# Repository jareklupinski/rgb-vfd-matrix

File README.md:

# rgb-vfd-matrix
An interface board for displaying images on a unique display

Trawling ebay one day I stumbled across the IGG4-64x64M2. It seemed like an interesting piece and a good challenge, so I designed a board to easily feed it pixel data from any microcontroller.

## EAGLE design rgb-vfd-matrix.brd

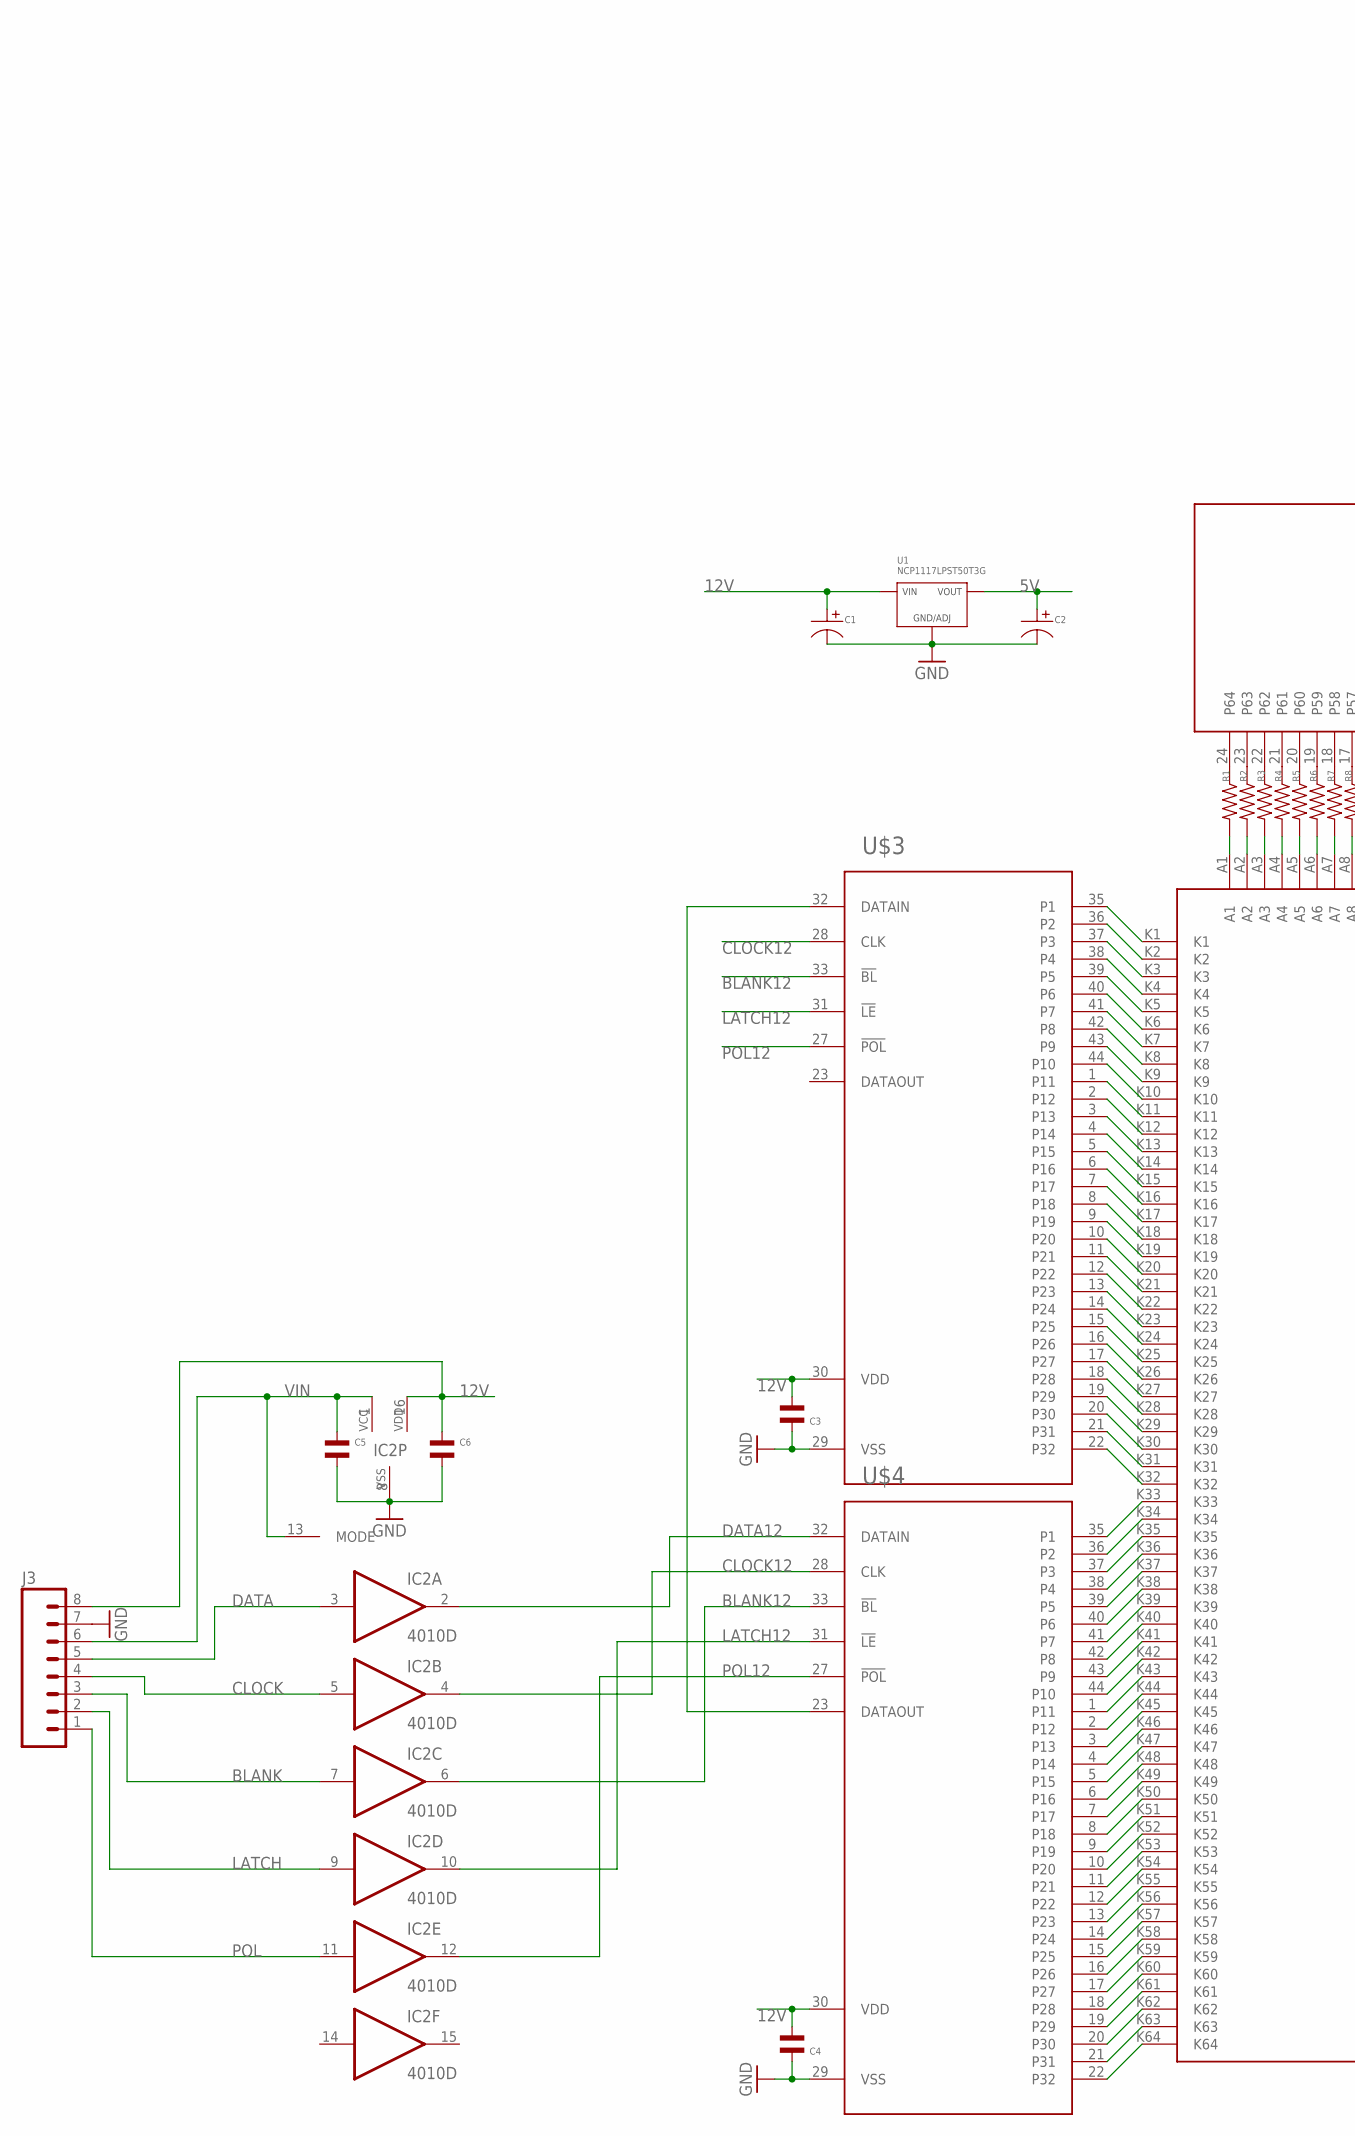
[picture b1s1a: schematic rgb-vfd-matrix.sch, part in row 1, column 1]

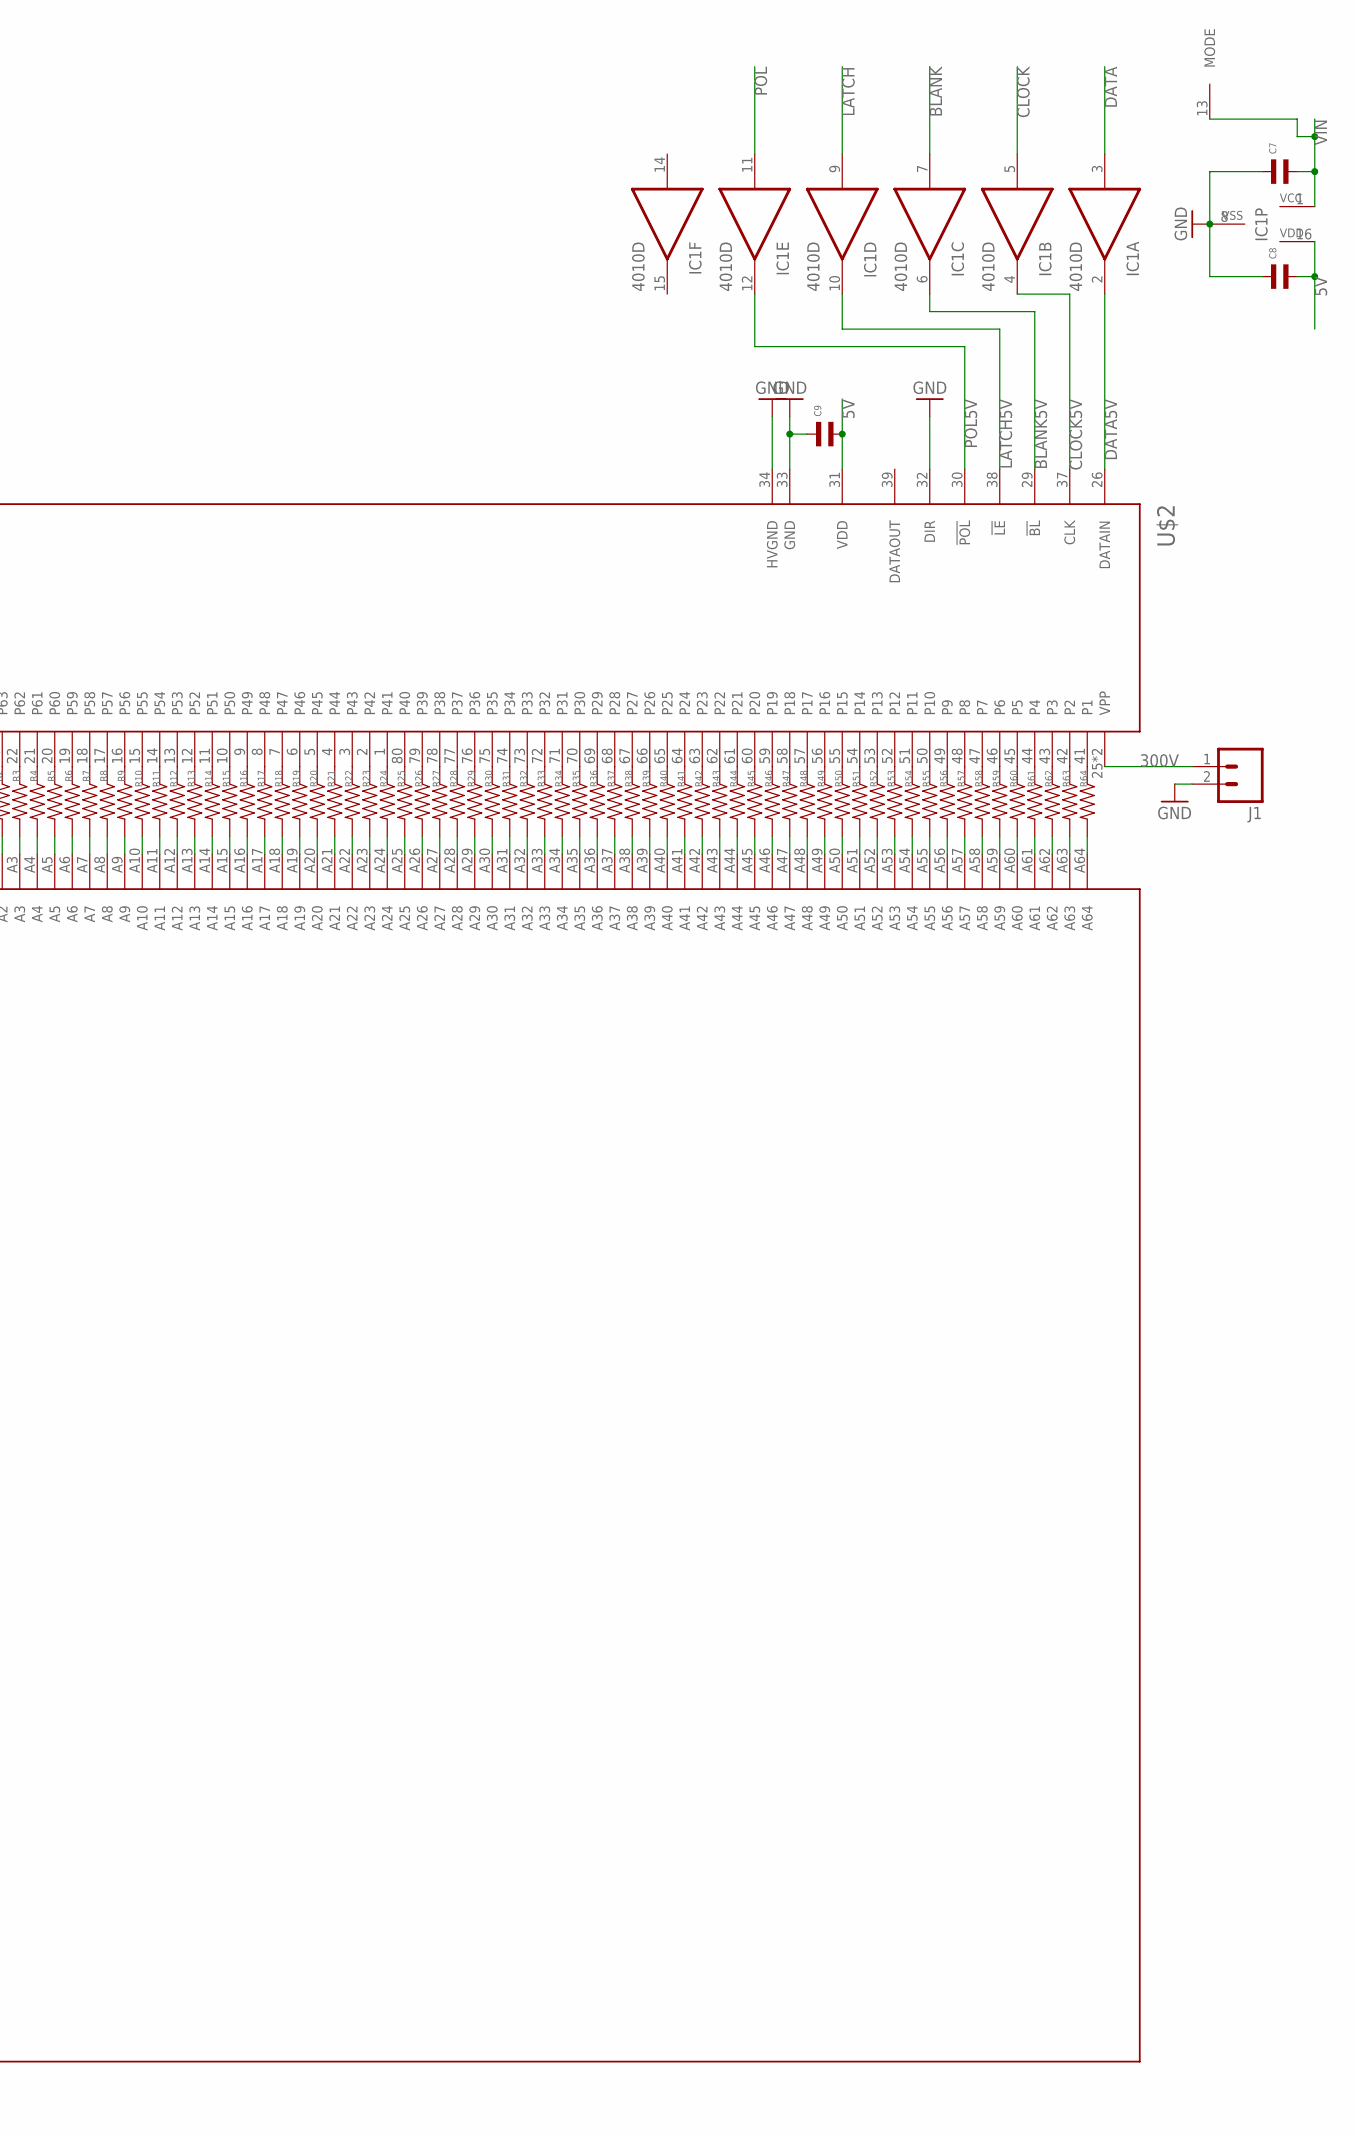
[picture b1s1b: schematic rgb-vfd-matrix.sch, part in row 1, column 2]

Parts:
C1, C2: CAPACITOR_P_8MM; CP8MM
C3, C4, C5, C6, C7, C8, C9: CAPACITOR_NP_0603; C0603
IC1, IC2: 4010D; SO16
J1: M023.5MM; SCREWTERMINAL-3.5MM-2
J3: M083.5MM-8; SCREWTERMINAL-3.5MM-8
R1, R2, R3, R4, R5, R6, R7, R8, R9, R10, R11, R12, R13, R14, R15, R16, R17, R18, R19, R20, R21, R22, R23, R24, R25, R26, R27, R28, R29, R30, R31, R32, R33, R34, R35, R36, R37, R38, R39, R40, R41, R42, R43, R44, R45, R46, R47, R48, R49, R50, R51, R52, R53, R54, R55, R56, R57, R58, R59, R60, R61, R62, R63, R64: RESISTOR_0805; R0805
U1: NCP1117LPST50T3G; SOT-223-3
U$1: RGBVFDMATRIX
U$2: HV507; PQFP80
U$3, U$4: HV5530; PQFP44

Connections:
5V: C2.P$1, C8.P$2, C9.P$2, IC1.16 (VDD), U1.P$1 (VOUT), U1.P$3 (VOUT), U$2.31 (VDD)
12V: C1.P$1, C3.P$2, C4.P$2, C6.P$1, IC2.16 (VDD), J3.8, U1.P$4 (VIN), U$3.30 (VDD), U$4.30 (VDD)
300V: J1.1, U$2.25 (VPP), U$2.40 (VPP)
BLANK: IC1.7 (I), IC2.7 (I), J3.3
BLANK5V: IC1.6 (O), U$2.29 (!BL)
BLANK12: IC2.6 (O), U$3.33 (!BL), U$4.33 (!BL)
CLOCK: IC1.5 (I), IC2.5 (I), J3.4
CLOCK5V: IC1.4 (O), U$2.37 (CLK)
CLOCK12: IC2.4 (O), U$3.28 (CLK), U$4.28 (CLK)
DATA: IC1.3 (I), IC2.3 (I), J3.5
DATA5V: IC1.2 (O), U$2.26 (DATAIN)
DATA12: IC2.2 (O), U$4.32 (DATAIN)
GND: C1.P$2, C2.P$2, C3.P$1, C4.P$1, C5.P$2, C6.P$2, C7.P$1, C8.P$1, C9.P$1, IC1.8 (VSS), IC2.8 (VSS), J1.2, J3.7, U1.P$2 (GND/ADJ), U$2.32 (DIR), U$2.33 (GND), U$2.34 (HVGND), U$3.29 (VSS), U$4.29 (VSS)
LATCH: IC1.9 (I), IC2.9 (I), J3.2
LATCH5V: IC1.10 (O), U$2.38 (!LE)
LATCH12: IC2.10 (O), U$3.31 (!LE), U$4.31 (!LE)
unnamed: R1.P$2, U$1.A1
unnamed: R2.P$2, U$1.A2
unnamed: R3.P$2, U$1.A3
unnamed: R4.P$2, U$1.A4
unnamed: R5.P$2, U$1.A5
unnamed: R6.P$2, U$1.A6
unnamed: R7.P$2, U$1.A7
unnamed: R8.P$2, U$1.A8
unnamed: R9.P$2, U$1.A9
unnamed: R10.P$2, U$1.A10
unnamed: R11.P$2, U$1.A11
unnamed: R12.P$2, U$1.A12
unnamed: R13.P$2, U$1.A13
unnamed: R14.P$2, U$1.A14
unnamed: R15.P$2, U$1.A15
unnamed: R16.P$2, U$1.A16
unnamed: R17.P$2, U$1.A17
unnamed: R18.P$2, U$1.A18
unnamed: R19.P$2, U$1.A19
unnamed: R20.P$2, U$1.A20
unnamed: R21.P$2, U$1.A21
unnamed: R22.P$2, U$1.A22
unnamed: R23.P$2, U$1.A23
unnamed: R24.P$2, U$1.A24
unnamed: R25.P$2, U$1.A25
unnamed: R26.P$2, U$1.A26
unnamed: R27.P$2, U$1.A27
unnamed: R28.P$2, U$1.A28
unnamed: R29.P$2, U$1.A29
unnamed: R30.P$2, U$1.A30
unnamed: R31.P$2, U$1.A31
unnamed: R32.P$2, U$1.A32
unnamed: R33.P$2, U$1.A33
unnamed: R34.P$2, U$1.A34
unnamed: R35.P$2, U$1.A35
unnamed: R36.P$2, U$1.A36
unnamed: R37.P$2, U$1.A37
unnamed: R38.P$2, U$1.A38
unnamed: R39.P$2, U$1.A39
unnamed: R40.P$2, U$1.A40
unnamed: R41.P$2, U$1.A41
unnamed: R42.P$2, U$1.A42
unnamed: R43.P$2, U$1.A43
unnamed: R44.P$2, U$1.A44
unnamed: R45.P$2, U$1.A45
unnamed: R46.P$2, U$1.A46
unnamed: R47.P$2, U$1.A47
unnamed: R48.P$2, U$1.A48
unnamed: R49.P$2, U$1.A49
unnamed: R50.P$2, U$1.A50
unnamed: R51.P$2, U$1.A51
unnamed: R52.P$2, U$1.A52
unnamed: R53.P$2, U$1.A53
unnamed: R54.P$2, U$1.A54
unnamed: R55.P$2, U$1.A55
unnamed: R56.P$2, U$1.A56
unnamed: R57.P$2, U$1.A57
unnamed: R58.P$2, U$1.A58
unnamed: R59.P$2, U$1.A59
unnamed: R60.P$2, U$1.A60
unnamed: R61.P$2, U$1.A61
unnamed: R62.P$2, U$1.A62
unnamed: R63.P$2, U$1.A63
unnamed: R64.P$2, U$1.A64
unnamed: R1.P$1, U$2.24 (P64)
unnamed: U$1.K1, U$3.35 (P1)
unnamed: R2.P$1, U$2.23 (P63)
unnamed: R3.P$1, U$2.22 (P62)
unnamed: R4.P$1, U$2.21 (P61)
unnamed: R5.P$1, U$2.20 (P60)
unnamed: R6.P$1, U$2.19 (P59)
unnamed: R7.P$1, U$2.18 (P58)
unnamed: R8.P$1, U$2.17 (P57)
unnamed: R9.P$1, U$2.16 (P56)
unnamed: R10.P$1, U$2.15 (P55)
unnamed: R11.P$1, U$2.14 (P54)
unnamed: R12.P$1, U$2.13 (P53)
unnamed: R13.P$1, U$2.12 (P52)
unnamed: R14.P$1, U$2.11 (P51)
unnamed: R15.P$1, U$2.10 (P50)
unnamed: R16.P$1, U$2.9 (P49)
unnamed: R17.P$1, U$2.8 (P48)
unnamed: R18.P$1, U$2.7 (P47)
unnamed: R19.P$1, U$2.6 (P46)
unnamed: R20.P$1, U$2.5 (P45)
unnamed: R21.P$1, U$2.4 (P44)
unnamed: R22.P$1, U$2.3 (P43)
unnamed: R23.P$1, U$2.2 (P42)
unnamed: R24.P$1, U$2.1 (P41)
unnamed: R25.P$1, U$2.80 (P40)
unnamed: R26.P$1, U$2.79 (P39)
unnamed: R27.P$1, U$2.78 (P38)
unnamed: R28.P$1, U$2.77 (P37)
unnamed: R29.P$1, U$2.76 (P36)
unnamed: R30.P$1, U$2.75 (P35)
unnamed: R31.P$1, U$2.74 (P34)
unnamed: R32.P$1, U$2.73 (P33)
unnamed: R33.P$1, U$2.72 (P32)
unnamed: R34.P$1, U$2.71 (P31)
unnamed: R35.P$1, U$2.70 (P30)
unnamed: R36.P$1, U$2.69 (P29)
unnamed: R37.P$1, U$2.68 (P28)
unnamed: R38.P$1, U$2.67 (P27)
unnamed: R39.P$1, U$2.66 (P26)
unnamed: R40.P$1, U$2.65 (P25)
unnamed: R41.P$1, U$2.64 (P24)
unnamed: R42.P$1, U$2.63 (P23)
unnamed: R43.P$1, U$2.62 (P22)
unnamed: R44.P$1, U$2.61 (P21)
unnamed: R45.P$1, U$2.60 (P20)
unnamed: R46.P$1, U$2.59 (P19)
unnamed: R47.P$1, U$2.58 (P18)
unnamed: R48.P$1, U$2.57 (P17)
unnamed: R49.P$1, U$2.56 (P16)
unnamed: R50.P$1, U$2.55 (P15)
unnamed: R51.P$1, U$2.54 (P14)
unnamed: R52.P$1, U$2.53 (P13)
unnamed: R53.P$1, U$2.52 (P12)
unnamed: R54.P$1, U$2.51 (P11)
unnamed: R55.P$1, U$2.50 (P10)
unnamed: R56.P$1, U$2.49 (P9)
unnamed: R57.P$1, U$2.48 (P8)
unnamed: R58.P$1, U$2.47 (P7)
unnamed: R59.P$1, U$2.46 (P6)
unnamed: R60.P$1, U$2.45 (P5)
unnamed: R61.P$1, U$2.44 (P4)
unnamed: R62.P$1, U$2.43 (P3)
unnamed: R63.P$1, U$2.42 (P2)
unnamed: R64.P$1, U$2.41 (P1)
unnamed: U$1.K2, U$3.36 (P2)
unnamed: U$1.K3, U$3.37 (P3)
unnamed: U$1.K4, U$3.38 (P4)
unnamed: U$1.K5, U$3.39 (P5)
unnamed: U$1.K6, U$3.40 (P6)
unnamed: U$1.K7, U$3.41 (P7)
unnamed: U$1.K8, U$3.42 (P8)
unnamed: U$1.K9, U$3.43 (P9)
unnamed: U$1.K10, U$3.44 (P10)
unnamed: U$1.K11, U$3.1 (P11)
unnamed: U$1.K12, U$3.2 (P12)
unnamed: U$1.K13, U$3.3 (P13)
unnamed: U$1.K14, U$3.4 (P14)
unnamed: U$1.K15, U$3.5 (P15)
unnamed: U$1.K16, U$3.6 (P16)
unnamed: U$1.K17, U$3.7 (P17)
unnamed: U$1.K18, U$3.8 (P18)
unnamed: U$1.K19, U$3.9 (P19)
unnamed: U$1.K20, U$3.10 (P20)
unnamed: U$1.K21, U$3.11 (P21)
unnamed: U$1.K22, U$3.12 (P22)
unnamed: U$1.K23, U$3.13 (P23)
unnamed: U$1.K24, U$3.14 (P24)
unnamed: U$1.K25, U$3.15 (P25)
unnamed: U$1.K26, U$3.16 (P26)
unnamed: U$1.K27, U$3.17 (P27)
unnamed: U$1.K28, U$3.18 (P28)
unnamed: U$1.K29, U$3.19 (P29)
unnamed: U$1.K30, U$3.20 (P30)
unnamed: U$1.K31, U$3.21 (P31)
unnamed: U$1.K32, U$3.22 (P32)
unnamed: U$1.K33, U$4.35 (P1)
unnamed: U$1.K34, U$4.36 (P2)
unnamed: U$1.K35, U$4.37 (P3)
unnamed: U$1.K36, U$4.38 (P4)
unnamed: U$1.K37, U$4.39 (P5)
unnamed: U$1.K38, U$4.40 (P6)
unnamed: U$1.K39, U$4.41 (P7)
unnamed: U$1.K40, U$4.42 (P8)
unnamed: U$1.K41, U$4.43 (P9)
unnamed: U$1.K42, U$4.44 (P10)
unnamed: U$1.K43, U$4.1 (P11)
unnamed: U$1.K44, U$4.2 (P12)
unnamed: U$1.K45, U$4.3 (P13)
unnamed: U$1.K46, U$4.4 (P14)
unnamed: U$1.K47, U$4.5 (P15)
unnamed: U$1.K48, U$4.6 (P16)
unnamed: U$1.K49, U$4.7 (P17)
unnamed: U$1.K50, U$4.8 (P18)
unnamed: U$1.K51, U$4.9 (P19)
unnamed: U$1.K52, U$4.10 (P20)
unnamed: U$1.K53, U$4.11 (P21)
unnamed: U$1.K54, U$4.12 (P22)
unnamed: U$1.K55, U$4.13 (P23)
unnamed: U$1.K56, U$4.14 (P24)
unnamed: U$1.K57, U$4.15 (P25)
unnamed: U$1.K58, U$4.16 (P26)
unnamed: U$1.K59, U$4.17 (P27)
unnamed: U$1.K60, U$4.18 (P28)
unnamed: U$1.K61, U$4.19 (P29)
unnamed: U$1.K62, U$4.20 (P30)
unnamed: U$1.K63, U$4.21 (P31)
unnamed: U$3.32 (DATAIN), U$4.23 (DATAOUT)
unnamed: U$1.K64, U$4.22 (P32)
POL: IC1.11 (I), IC2.11 (I), J3.1
POL5V: IC1.12 (O), U$2.30 (!POL)
POL12: IC2.12 (O), U$3.27 (!POL), U$4.27 (!POL)
VIN: C5.P$1, C7.P$2, IC1.1 (VCC), IC1.13 (MODE), IC2.1 (VCC), IC2.13 (MODE), J3.6

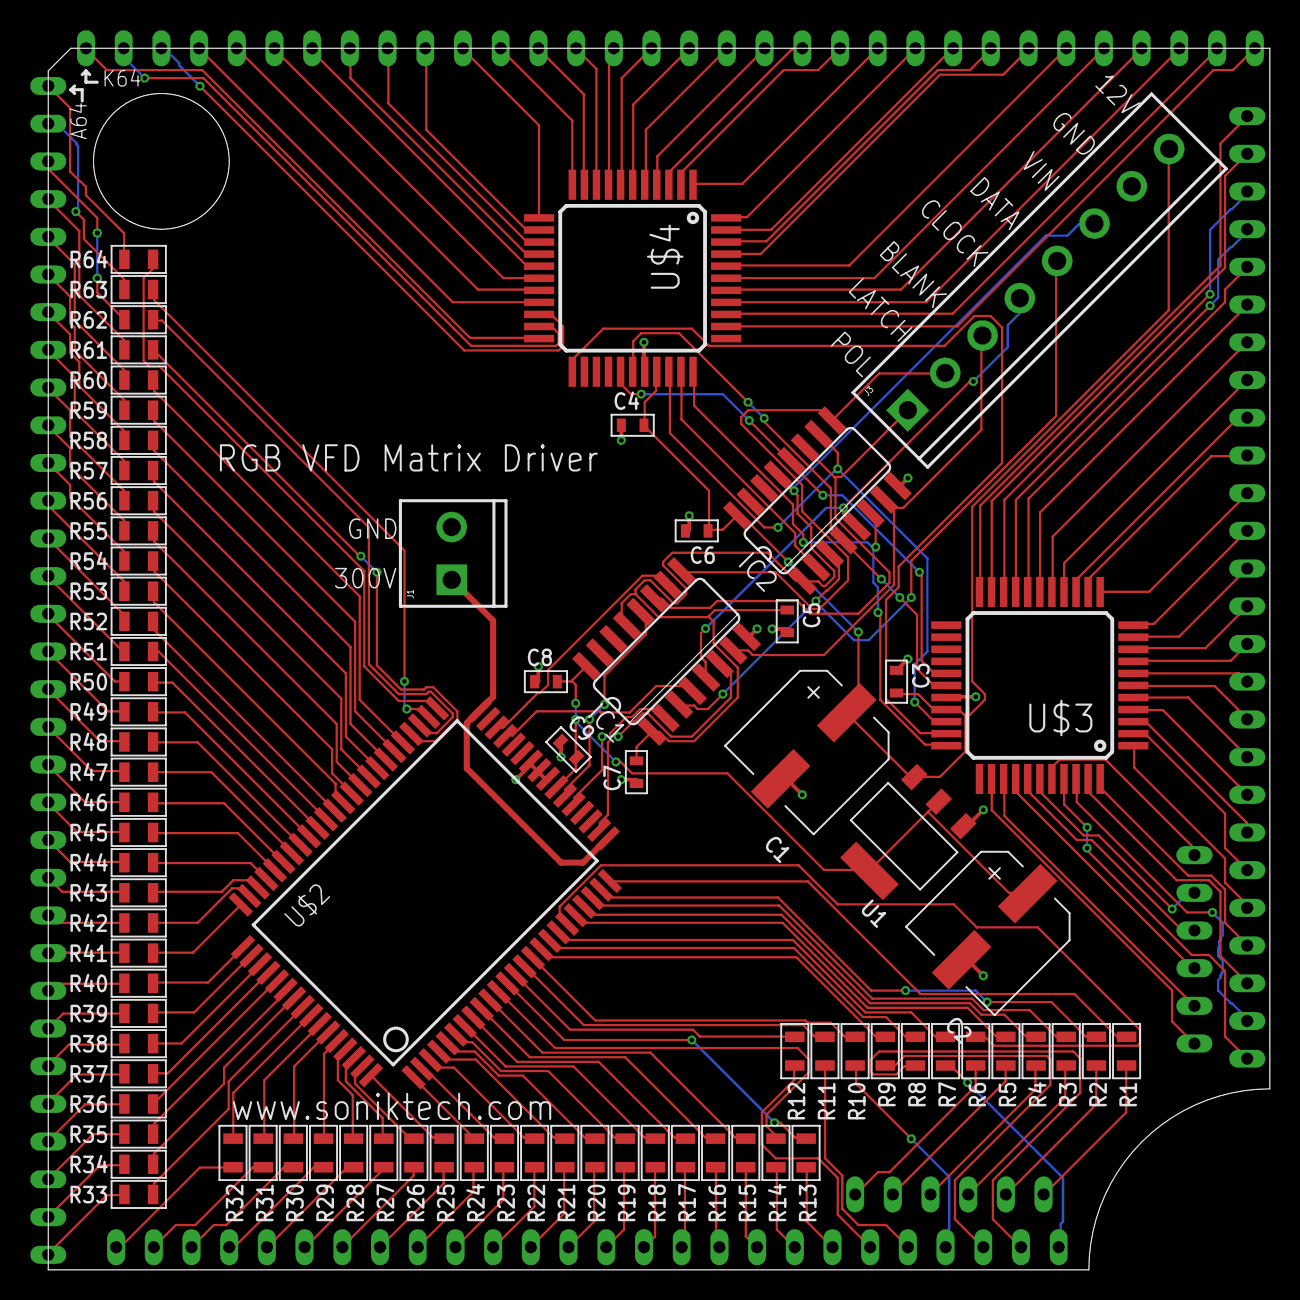
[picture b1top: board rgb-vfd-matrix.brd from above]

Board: 2 copper layers, 81.0 x 81.0 mm, 82 parts (0 on the bottom side), 213 nets.

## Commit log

2018-07-05 design tested: working

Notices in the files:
parts and their libraries:
SparkFun-Connectors: Licensing: Creative Commons ShareAlike 4.0 International - https://creativecommons.org/licenses/by-sa/4.0
40xx: Source: www.fairchildsemi.com CD4010.pdf  © 2000 Fairchild Semiconductor Corporation DS005945
